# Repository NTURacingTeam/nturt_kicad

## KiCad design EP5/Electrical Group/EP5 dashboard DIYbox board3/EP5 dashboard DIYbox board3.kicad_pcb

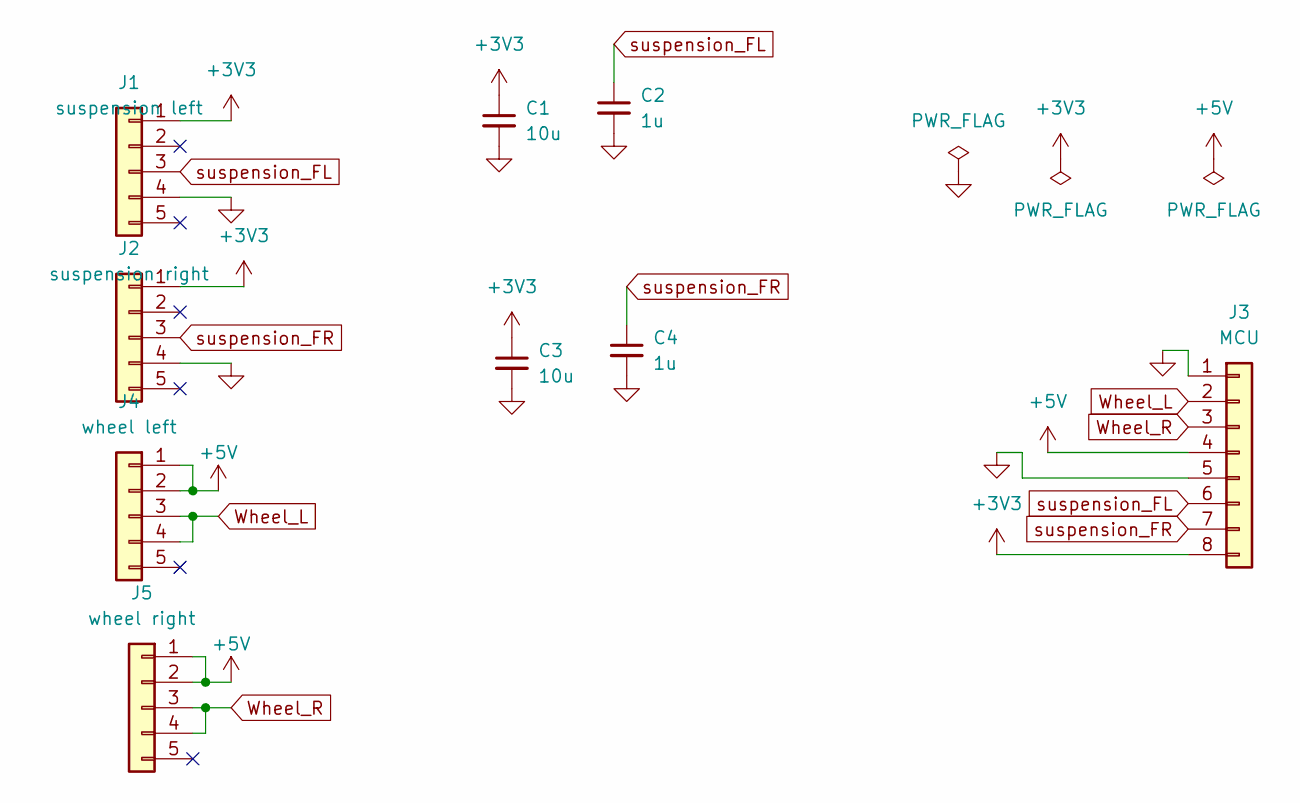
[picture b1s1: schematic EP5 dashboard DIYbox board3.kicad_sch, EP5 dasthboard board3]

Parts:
C1, C3: 10u; C_0805_2012Metric
C2, C4: 1u; C_0805_2012Metric
J1: suspension left; WP-03F3-09-11
J2: suspension right; WP-03F3-09-11
J3: MCU; JST_XH_S8B-XH-A_1x08_P2.50mm_Horizontal
J4: wheel left; WP-04F3-26-11
J5: wheel right; WP-04F3-26-11

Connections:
+3V3: C1.1, C3.1, J1.1, J2.1, J3.8
+5V: J3.4, J4.1, J4.2, J5.1, J5.2
GND: C1.2, C2.2, C3.2, C4.2, J1.4, J2.4, J3.1, J3.5
Wheel_L: J3.2, J4.3, J4.4
Wheel_R: J3.3, J5.3, J5.4
suspension_FL: C2.1, J1.3, J3.6
suspension_FR: C4.1, J2.3, J3.7

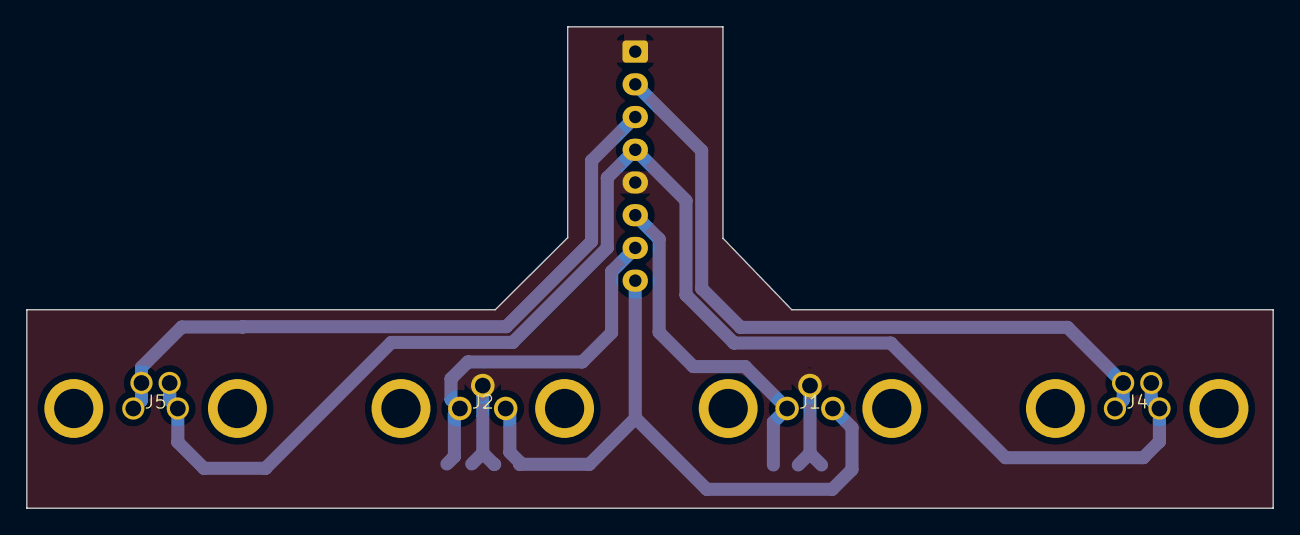
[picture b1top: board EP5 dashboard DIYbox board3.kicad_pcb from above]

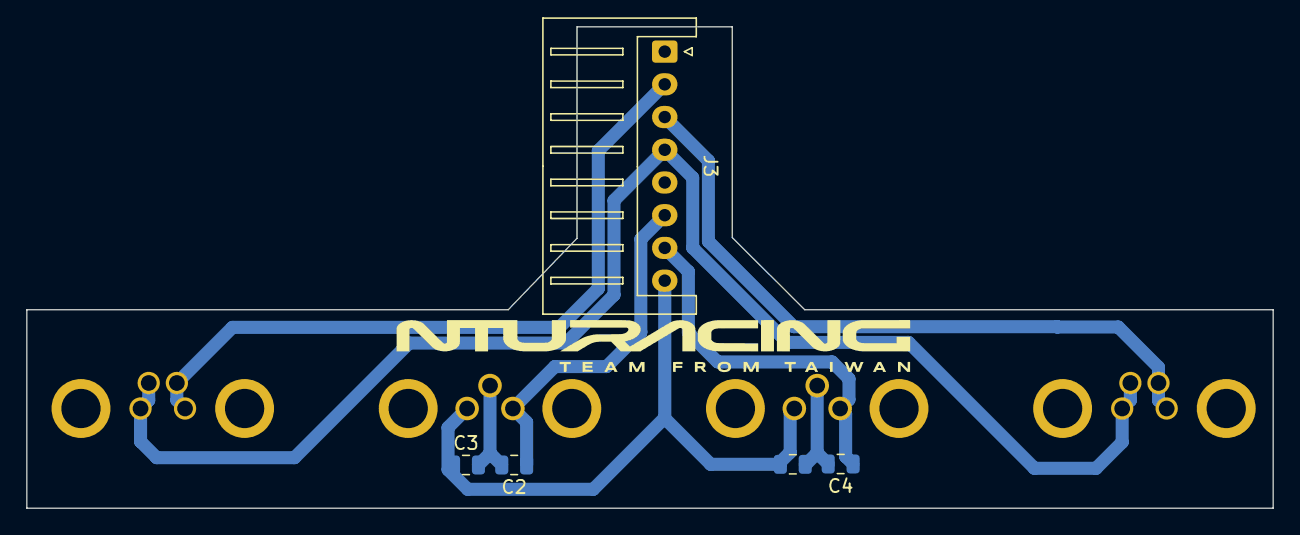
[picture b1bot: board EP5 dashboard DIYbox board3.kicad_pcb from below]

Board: 2 copper layers, 95.2 x 36.8 mm, 9 parts (5 on the bottom side), 7 nets.

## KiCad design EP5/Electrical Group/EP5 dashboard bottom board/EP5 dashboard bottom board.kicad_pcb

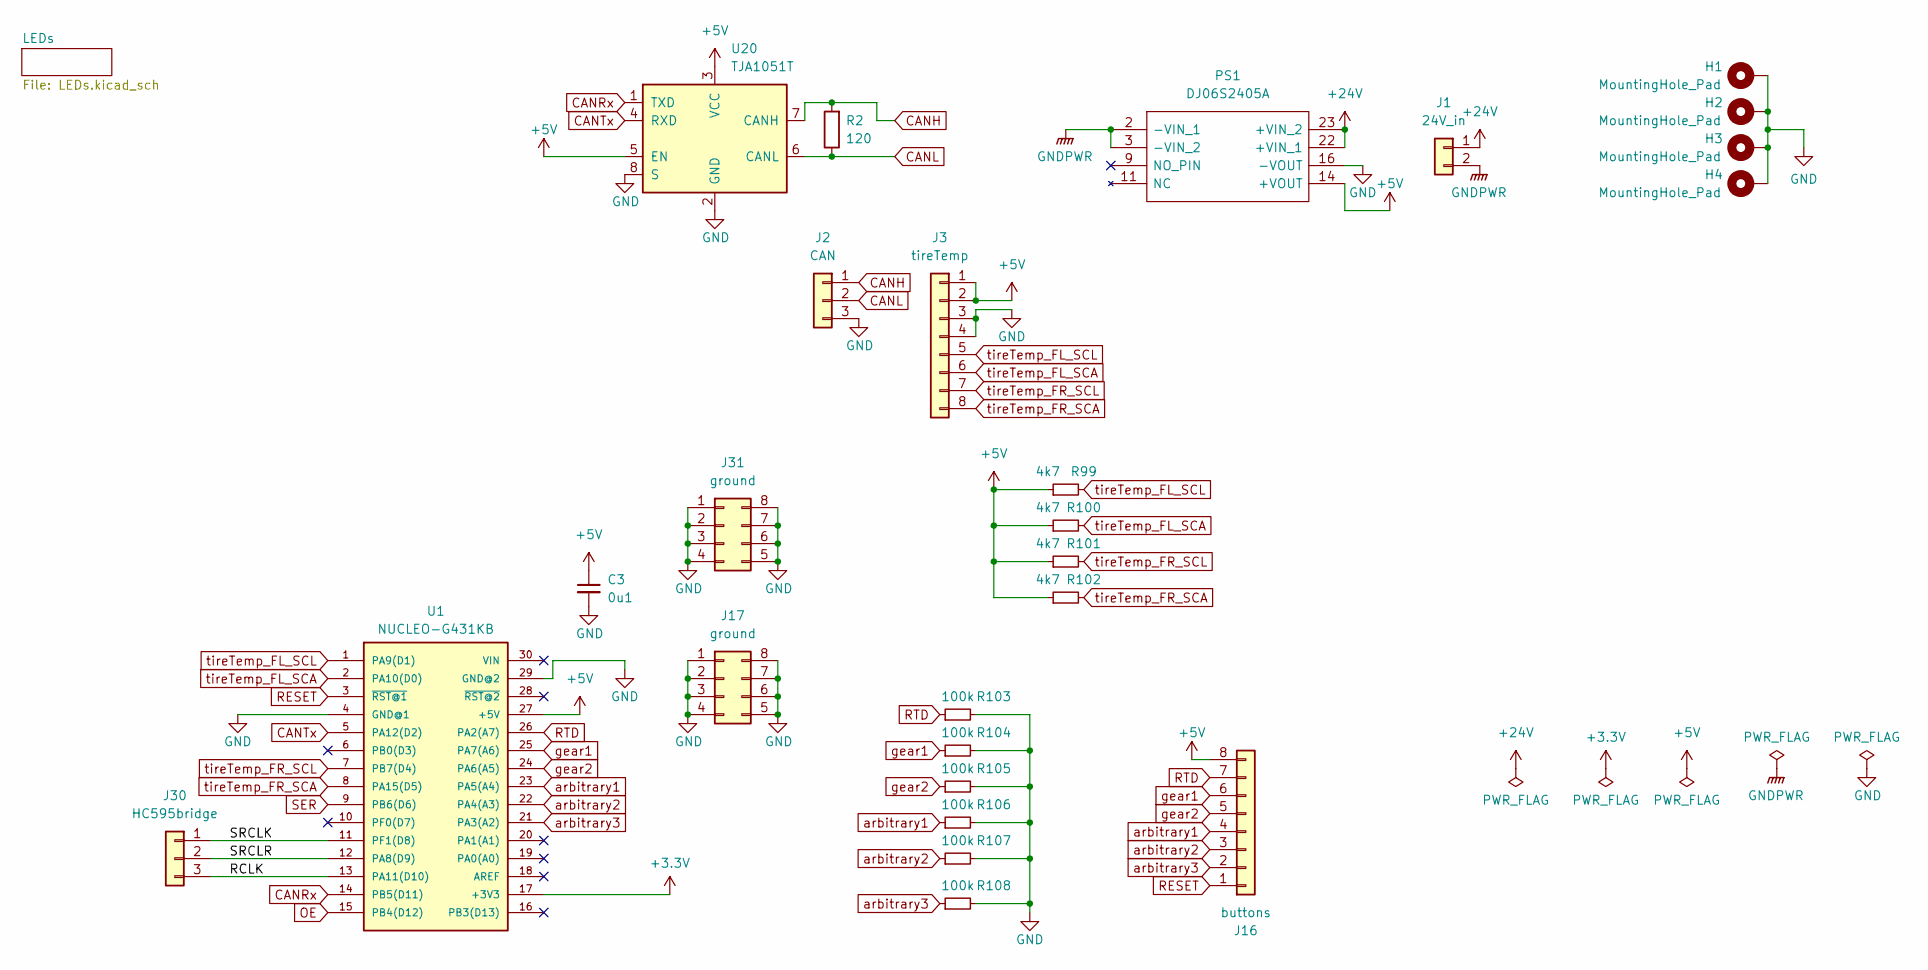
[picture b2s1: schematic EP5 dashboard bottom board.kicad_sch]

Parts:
C3: 0u1; C_0805_2012Metric_Pad1.18x1.45mm_HandSolder
H1, H2, H3, H4: MountingHole_Pad; MountingHole_2.2mm_M2_DIN965_Pad_TopBottom
J1: 24V_in; JST_XH_S2B-XH-A-1_1x02_P2.50mm_Horizontal
J2: CAN; JST_XH_S3B-XH-A-1_1x03_P2.50mm_Horizontal
J3: tireTemp; JST_XH_S8B-XH-A-1_1x08_P2.50mm_Horizontal
J16: buttons; JST_XH_S8B-XH-A-1_1x08_P2.50mm_Horizontal
J17, J31: ground; PinSocket_2x04_P1.27mm_Vertical
J30: HC595bridge; PinSocket_1x03_P1.27mm_Vertical
PS1: DJ06S2405A; DJ06S4805A; Mouser Part Number 108-DJ06S4805A
R2: 120; R_0805_2012Metric
R99, R100, R101, R102: 4k7; R_0805_2012Metric
R103, R104, R105, R106, R107, R108: 100k; R_0805_2012Metric
U1: NUCLEO-G431KB; MANUFACTURER_PART_NUMBER NUCLEO-F303K8
U20: TJA1051T; SOIC-8_3.9x4.9mm_P1.27mm

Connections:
+3.3V: U1.17 (+3V3)
+5V: C3.1, J3.1, J3.2, J16.8, PS1.14 (+VOUT), R99.1, R100.1, R101.1, R102.1, U1.27 (+5V), U20.3 (VCC), U20.5 (EN); also elsewhere on the board
+24V: J1.1, PS1.22 (+VIN_1), PS1.23 (+VIN_2)
/RCLK: J30.3, U1.13 (PA11(D10))
/SRCLK: J30.1, U1.11 (PF1(D8))
/SRCLR: J30.2, U1.12 (PA8(D9))
CANH: J2.1, R2.2, U20.7 (CANH)
CANL: J2.2, R2.1, U20.6 (CANL)
CANRx: U1.14 (PB5(D11)), U20.1 (TXD)
CANTx: U1.5 (PA12(D2)), U20.4 (RXD)
GND: C3.2, H1.1, H2.1, H3.1, H4.1, J2.3, J3.3, J3.4, J17.1, J17.2, J17.3, J17.4, J17.5, J17.6, J17.7, J17.8, J31.1, J31.2, J31.3, J31.4, J31.5, J31.6, J31.7, J31.8, PS1.16 (-VOUT), R103.2, R104.2, R105.2, R106.2, R107.2, R108.2, U1.4 (GND@1), U1.29 (GND@2), U20.2 (GND), U20.8 (S); also elsewhere on the board
GNDPWR: J1.2, PS1.2 (-VIN_1), PS1.3 (-VIN_2)
OE: U1.15 (PB4(D12)); also elsewhere on the board
RESET: J16.1, U1.3 (~RST@1)
RTD: J16.7, R103.1, U1.26 (PA2(A7))
SER: U1.9 (PB6(D6)); also elsewhere on the board
arbitrary1: J16.4, R106.1, U1.23 (PA5(A4))
arbitrary2: J16.3, R107.1, U1.22 (PA4(A3))
arbitrary3: J16.2, R108.1, U1.21 (PA3(A2))
gear1: J16.6, R104.1, U1.25 (PA7(A6))
gear2: J16.5, R105.1, U1.24 (PA6(A5))
tireTemp_FL_SCA: J3.6, R100.2, U1.2 (PA10(D0))
tireTemp_FL_SCL: J3.5, R99.2, U1.1 (PA9(D1))
tireTemp_FR_SCA: J3.8, R102.2, U1.8 (PA15(D5))
tireTemp_FR_SCL: J3.7, R101.2, U1.7 (PB7(D4))

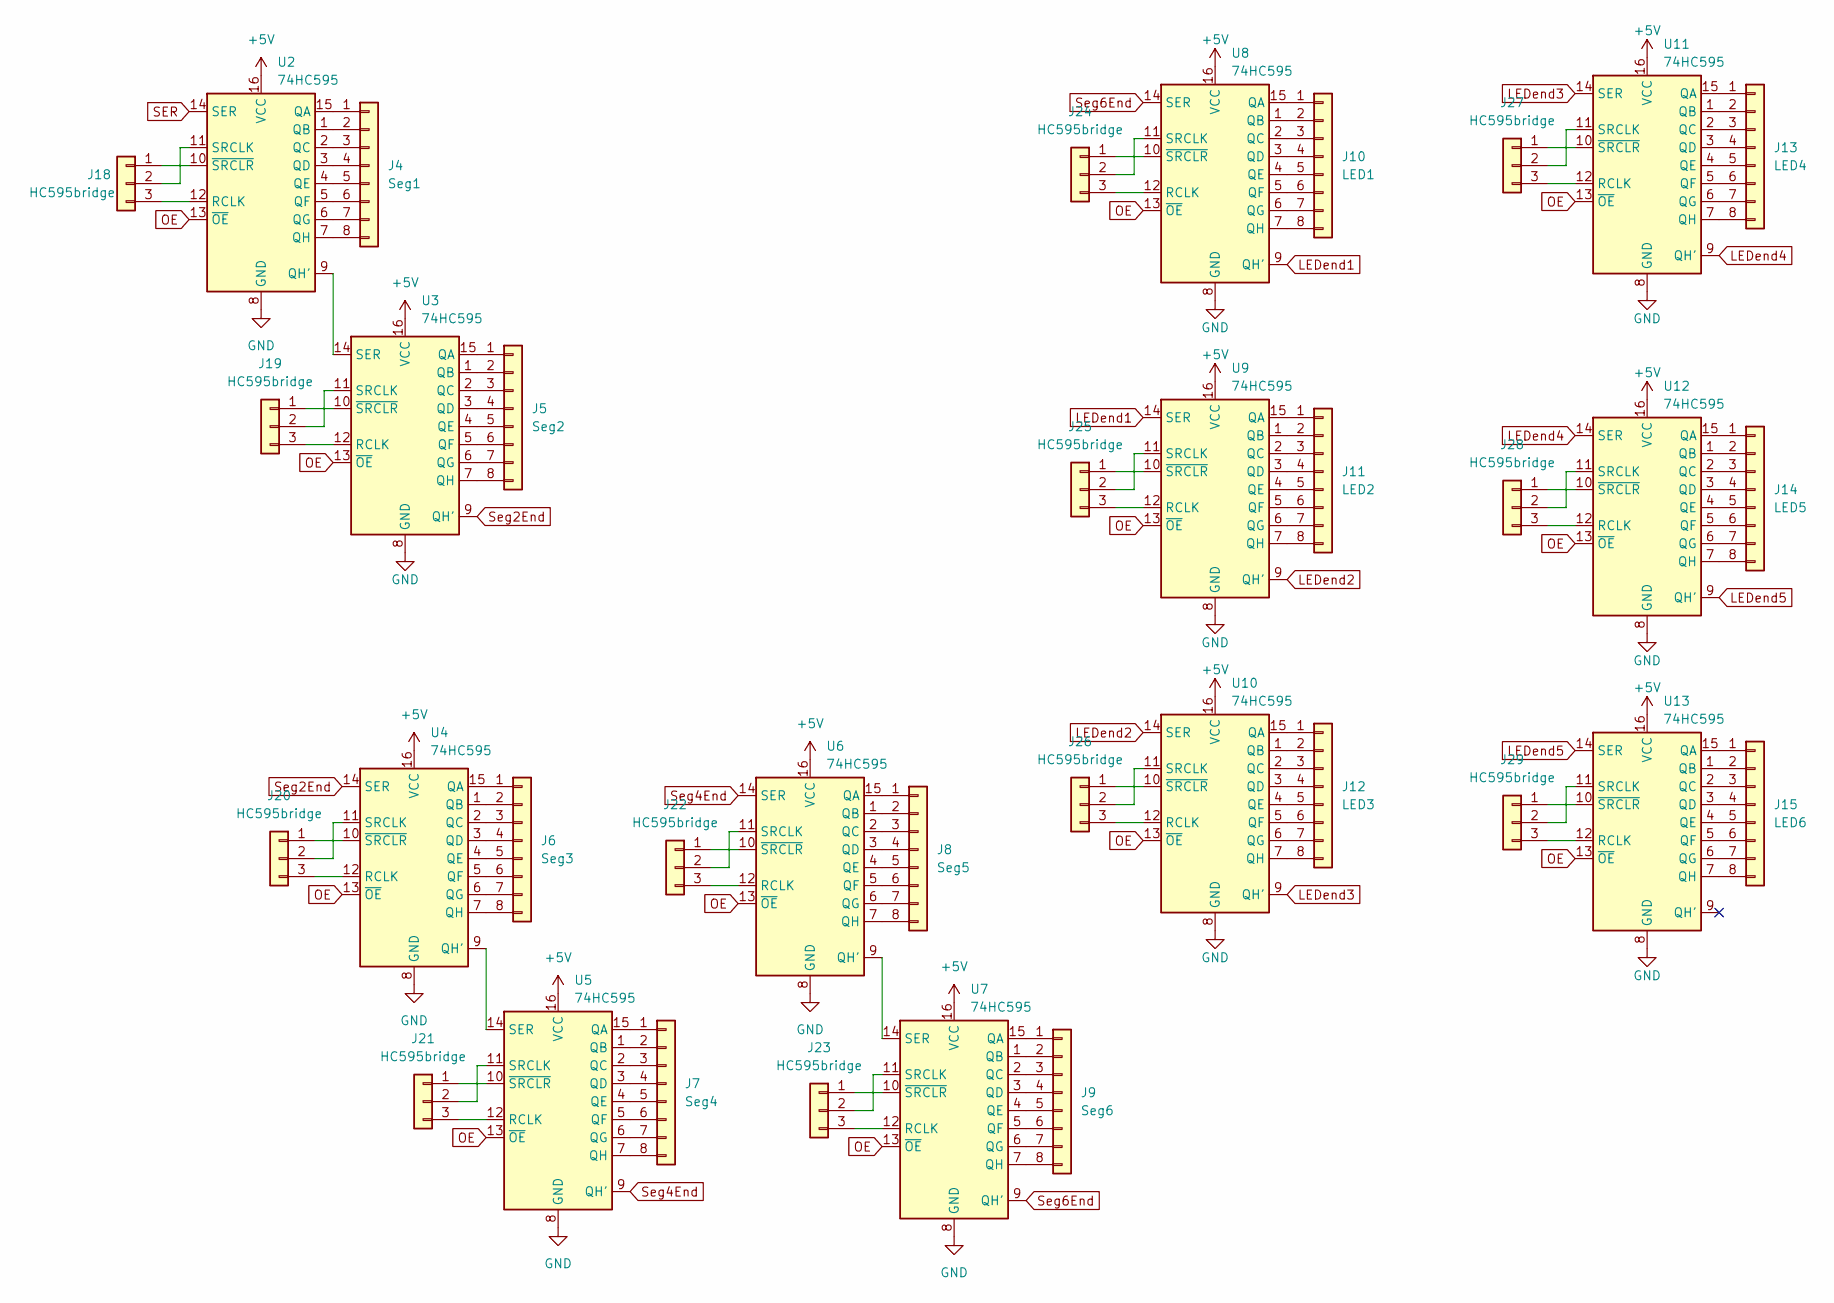
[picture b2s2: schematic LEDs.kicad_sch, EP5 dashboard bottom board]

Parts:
J4: Seg1; PinSocket_1x08_P1.27mm_Vertical
J5: Seg2; PinSocket_1x08_P1.27mm_Vertical
J6: Seg3; PinSocket_1x08_P1.27mm_Vertical
J7: Seg4; PinSocket_1x08_P1.27mm_Vertical
J8: Seg5; PinSocket_1x08_P1.27mm_Vertical
J9: Seg6; PinSocket_1x08_P1.27mm_Vertical
J10: LED1; PinSocket_1x08_P1.27mm_Vertical
J11: LED2; PinSocket_1x08_P1.27mm_Vertical
J12: LED3; PinSocket_1x08_P1.27mm_Vertical
J13: LED4; PinSocket_1x08_P1.27mm_Vertical
J14: LED5; PinSocket_1x08_P1.27mm_Vertical
J15: LED6; PinSocket_1x08_P1.27mm_Vertical
J18, J19, J20, J21, J22, J23, J24, J25, J26, J27, J28, J29: HC595bridge; PinSocket_1x03_P1.27mm_Vertical
U2, U3, U4, U5, U6, U7, U8, U9, U10, U11, U12, U13: 74HC595; SOIC-16_3.9x9.9mm_P1.27mm

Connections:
+5V: U2.16 (VCC), U3.16 (VCC), U4.16 (VCC), U5.16 (VCC), U6.16 (VCC), U7.16 (VCC), U8.16 (VCC), U9.16 (VCC), U10.16 (VCC), U11.16 (VCC), U12.16 (VCC), U13.16 (VCC); also elsewhere on the board
GND: U2.8 (GND), U3.8 (GND), U4.8 (GND), U5.8 (GND), U6.8 (GND), U7.8 (GND), U8.8 (GND), U9.8 (GND), U10.8 (GND), U11.8 (GND), U12.8 (GND), U13.8 (GND); also elsewhere on the board
LEDend1: U8.9 (QH'), U9.14 (SER)
LEDend2: U9.9 (QH'), U10.14 (SER)
LEDend3: U10.9 (QH'), U11.14 (SER)
LEDend4: U11.9 (QH'), U12.14 (SER)
LEDend5: U12.9 (QH'), U13.14 (SER)
unnamed: J4.1, U2.15 (QA)
unnamed: J4.2, U2.1 (QB)
unnamed: J4.3, U2.2 (QC)
unnamed: J4.4, U2.3 (QD)
unnamed: J4.5, U2.4 (QE)
unnamed: J4.6, U2.5 (QF)
unnamed: J4.7, U2.6 (QG)
unnamed: J4.8, U2.7 (QH)
unnamed: J5.1, U3.15 (QA)
unnamed: J5.2, U3.1 (QB)
unnamed: J5.3, U3.2 (QC)
unnamed: J5.4, U3.3 (QD)
unnamed: J5.5, U3.4 (QE)
unnamed: J5.6, U3.5 (QF)
unnamed: J5.7, U3.6 (QG)
unnamed: J5.8, U3.7 (QH)
unnamed: J6.1, U4.15 (QA)
unnamed: J6.2, U4.1 (QB)
unnamed: J6.3, U4.2 (QC)
unnamed: J6.4, U4.3 (QD)
unnamed: J6.5, U4.4 (QE)
unnamed: J6.6, U4.5 (QF)
unnamed: J6.7, U4.6 (QG)
unnamed: J6.8, U4.7 (QH)
unnamed: J7.1, U5.15 (QA)
unnamed: J7.2, U5.1 (QB)
unnamed: J7.3, U5.2 (QC)
unnamed: J7.4, U5.3 (QD)
unnamed: J7.5, U5.4 (QE)
unnamed: J7.6, U5.5 (QF)
unnamed: J7.7, U5.6 (QG)
unnamed: J7.8, U5.7 (QH)
unnamed: J8.1, U6.15 (QA)
unnamed: J8.2, U6.1 (QB)
unnamed: J8.3, U6.2 (QC)
unnamed: J8.4, U6.3 (QD)
unnamed: J8.5, U6.4 (QE)
unnamed: J8.6, U6.5 (QF)
unnamed: J8.7, U6.6 (QG)
unnamed: J8.8, U6.7 (QH)
unnamed: J9.1, U7.15 (QA)
unnamed: J9.2, U7.1 (QB)
unnamed: J9.3, U7.2 (QC)
unnamed: J9.4, U7.3 (QD)
unnamed: J9.5, U7.4 (QE)
unnamed: J9.6, U7.5 (QF)
unnamed: J9.7, U7.6 (QG)
unnamed: J9.8, U7.7 (QH)
unnamed: J10.1, U8.15 (QA)
unnamed: J10.2, U8.1 (QB)
unnamed: J10.3, U8.2 (QC)
unnamed: J10.4, U8.3 (QD)
unnamed: J10.5, U8.4 (QE)
unnamed: J10.6, U8.5 (QF)
unnamed: J10.7, U8.6 (QG)
unnamed: J10.8, U8.7 (QH)
unnamed: J11.1, U9.15 (QA)
unnamed: J11.2, U9.1 (QB)
unnamed: J11.3, U9.2 (QC)
unnamed: J11.4, U9.3 (QD)
unnamed: J11.5, U9.4 (QE)
unnamed: J11.6, U9.5 (QF)
unnamed: J11.7, U9.6 (QG)
unnamed: J11.8, U9.7 (QH)
unnamed: J12.1, U10.15 (QA)
unnamed: J12.2, U10.1 (QB)
unnamed: J12.3, U10.2 (QC)
unnamed: J12.4, U10.3 (QD)
unnamed: J12.5, U10.4 (QE)
unnamed: J12.6, U10.5 (QF)
unnamed: J12.7, U10.6 (QG)
unnamed: J12.8, U10.7 (QH)
unnamed: J13.1, U11.15 (QA)
unnamed: J13.2, U11.1 (QB)
unnamed: J13.3, U11.2 (QC)
unnamed: J13.4, U11.3 (QD)
unnamed: J13.5, U11.4 (QE)
unnamed: J13.6, U11.5 (QF)
unnamed: J13.7, U11.6 (QG)
unnamed: J13.8, U11.7 (QH)
unnamed: J14.1, U12.15 (QA)
unnamed: J14.2, U12.1 (QB)
unnamed: J14.3, U12.2 (QC)
unnamed: J14.4, U12.3 (QD)
unnamed: J14.5, U12.4 (QE)
unnamed: J14.6, U12.5 (QF)
unnamed: J14.7, U12.6 (QG)
unnamed: J14.8, U12.7 (QH)
unnamed: J15.1, U13.15 (QA)
unnamed: J15.2, U13.1 (QB)
unnamed: J15.3, U13.2 (QC)
unnamed: J15.4, U13.3 (QD)
unnamed: J15.5, U13.4 (QE)
unnamed: J15.6, U13.5 (QF)
unnamed: J15.7, U13.6 (QG)
unnamed: J15.8, U13.7 (QH)
unnamed: J18.1, U2.10 (~SRCLR)
unnamed: J18.2, U2.11 (SRCLK)
unnamed: J18.3, U2.12 (RCLK)
unnamed: J19.1, U3.10 (~SRCLR)
unnamed: J19.2, U3.11 (SRCLK)
unnamed: J19.3, U3.12 (RCLK)
unnamed: J20.1, U4.10 (~SRCLR)
unnamed: J20.2, U4.11 (SRCLK)
unnamed: J20.3, U4.12 (RCLK)
unnamed: J21.1, U5.10 (~SRCLR)
unnamed: J21.2, U5.11 (SRCLK)
unnamed: J21.3, U5.12 (RCLK)
unnamed: J22.1, U6.10 (~SRCLR)
unnamed: J22.2, U6.11 (SRCLK)
unnamed: J22.3, U6.12 (RCLK)
unnamed: J23.1, U7.10 (~SRCLR)
unnamed: J23.2, U7.11 (SRCLK)
unnamed: J23.3, U7.12 (RCLK)
unnamed: J24.1, U8.10 (~SRCLR)
unnamed: J24.2, U8.11 (SRCLK)
unnamed: J24.3, U8.12 (RCLK)
unnamed: J25.1, U9.10 (~SRCLR)
unnamed: J25.2, U9.11 (SRCLK)
unnamed: J25.3, U9.12 (RCLK)
unnamed: J26.1, U10.10 (~SRCLR)
unnamed: J26.2, U10.11 (SRCLK)
unnamed: J26.3, U10.12 (RCLK)
unnamed: J27.1, U11.10 (~SRCLR)
unnamed: J27.2, U11.11 (SRCLK)
unnamed: J27.3, U11.12 (RCLK)
unnamed: J28.1, U12.10 (~SRCLR)
unnamed: J28.2, U12.11 (SRCLK)
unnamed: J28.3, U12.12 (RCLK)
unnamed: J29.1, U13.10 (~SRCLR)
unnamed: J29.2, U13.11 (SRCLK)
unnamed: J29.3, U13.12 (RCLK)
unnamed: U2.9 (QH'), U3.14 (SER)
unnamed: U4.9 (QH'), U5.14 (SER)
unnamed: U6.9 (QH'), U7.14 (SER)
OE: U2.13 (~OE), U3.13 (~OE), U4.13 (~OE), U5.13 (~OE), U6.13 (~OE), U7.13 (~OE), U8.13 (~OE), U9.13 (~OE), U10.13 (~OE), U11.13 (~OE), U12.13 (~OE), U13.13 (~OE); also elsewhere on the board
SER: U2.14 (SER); also elsewhere on the board
Seg2End: U3.9 (QH'), U4.14 (SER)
Seg4End: U5.9 (QH'), U6.14 (SER)
Seg6End: U7.9 (QH'), U8.14 (SER)

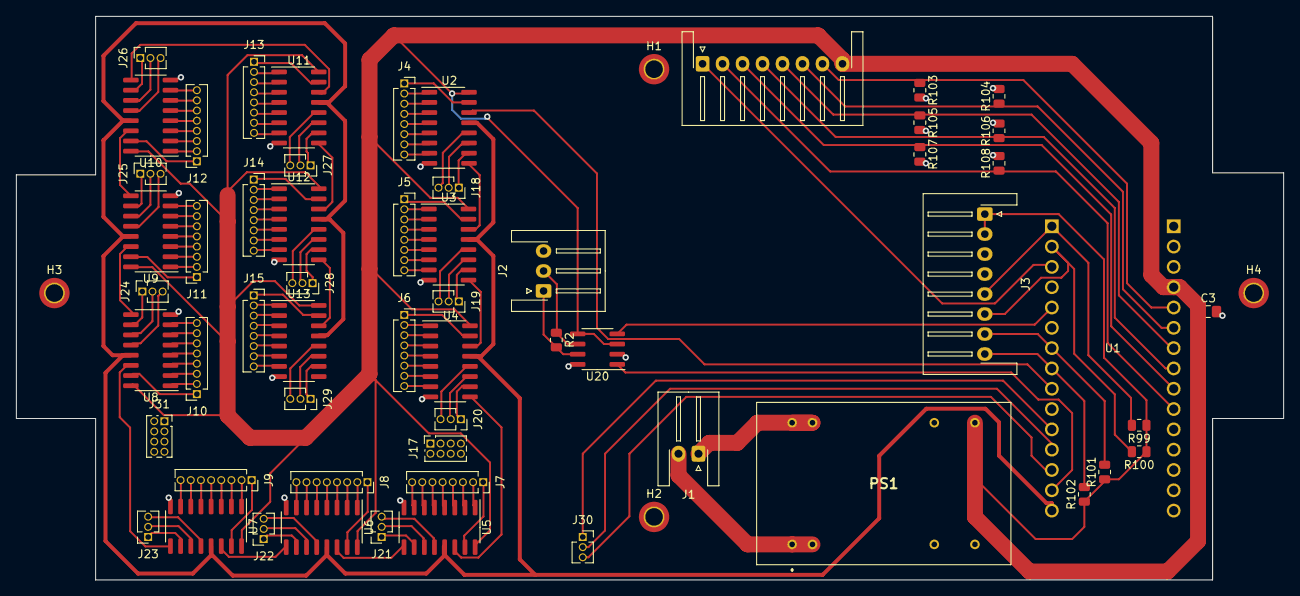
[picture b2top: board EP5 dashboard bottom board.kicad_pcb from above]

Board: 2 copper layers, 158.5 x 70.5 mm, 62 parts (0 on the bottom side), 167 nets.

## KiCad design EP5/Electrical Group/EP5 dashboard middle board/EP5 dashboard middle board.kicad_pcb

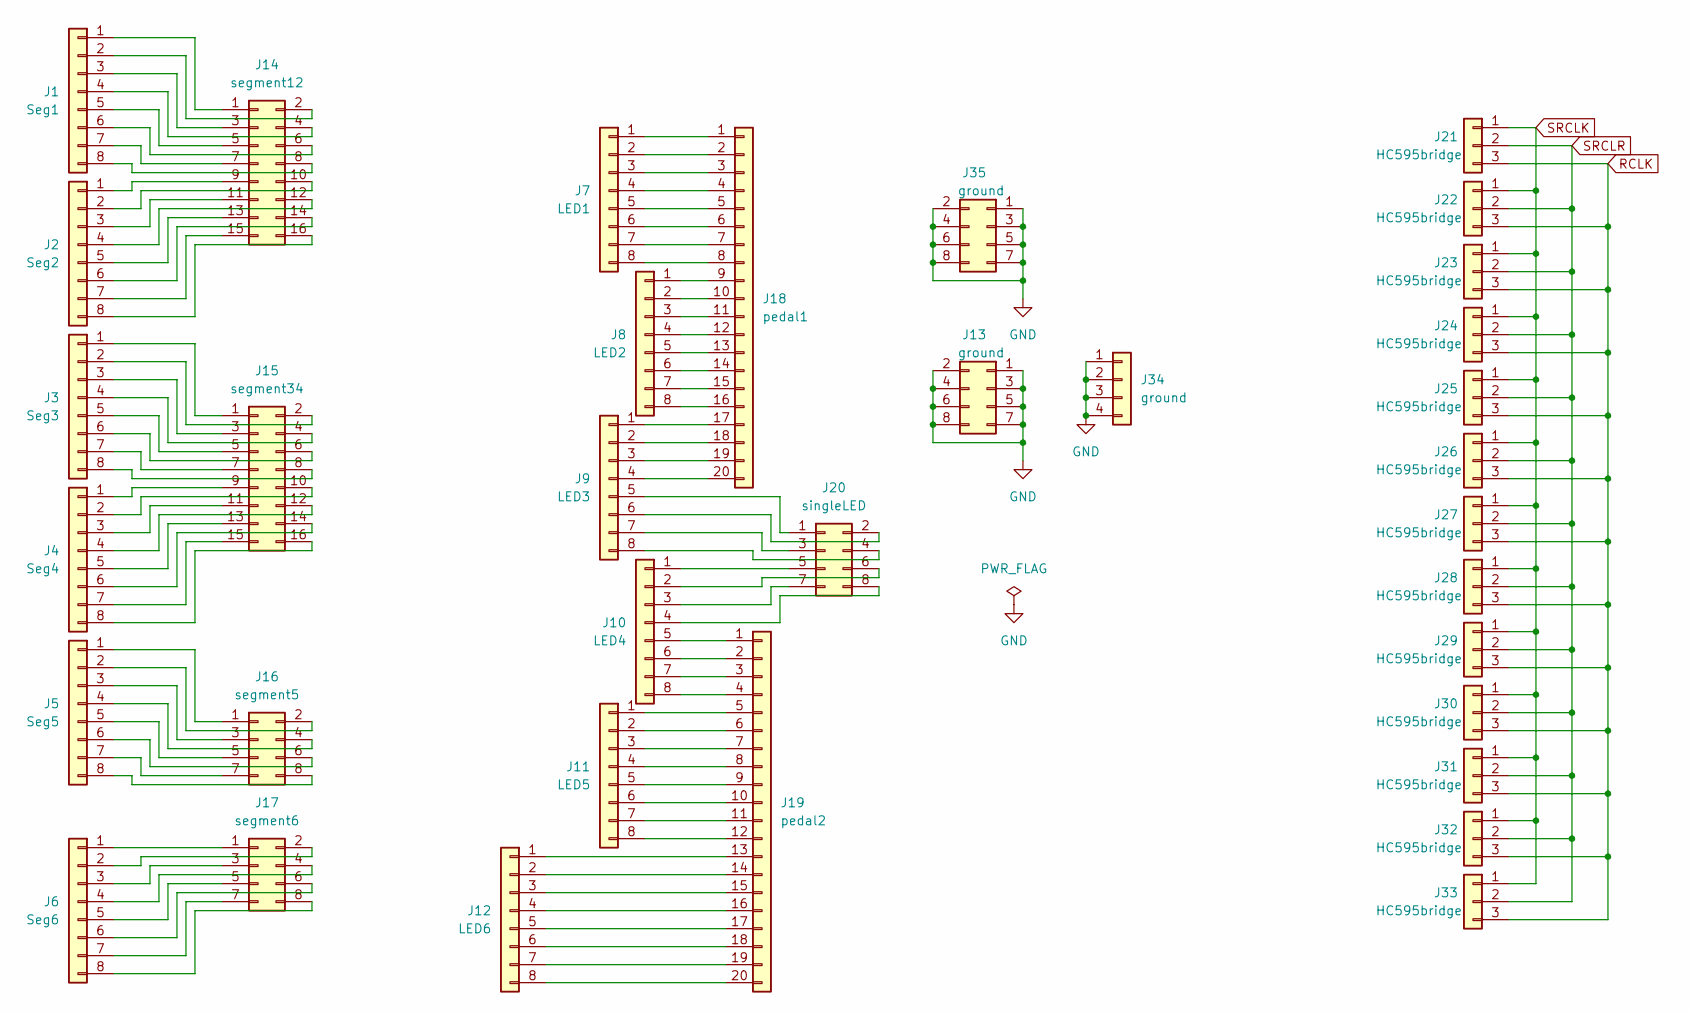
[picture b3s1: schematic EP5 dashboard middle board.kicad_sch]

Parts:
J1: Seg1; PinHeader_1x08_P1.27mm_Vertical
J2: Seg2; PinHeader_1x08_P1.27mm_Vertical
J3: Seg3; PinHeader_1x08_P1.27mm_Vertical
J4: Seg4; PinHeader_1x08_P1.27mm_Vertical
J5: Seg5; PinHeader_1x08_P1.27mm_Vertical
J6: Seg6; PinHeader_1x08_P1.27mm_Vertical
J7: LED1; PinHeader_1x08_P1.27mm_Vertical
J8: LED2; PinHeader_1x08_P1.27mm_Vertical
J9: LED3; PinHeader_1x08_P1.27mm_Vertical
J10: LED4; PinHeader_1x08_P1.27mm_Vertical
J11: LED5; PinHeader_1x08_P1.27mm_Vertical
J12: LED6; PinHeader_1x08_P1.27mm_Vertical
J13, J35: ground; PinHeader_2x04_P1.27mm_Vertical
J14: segment12; PinSocket_2x08_P2.54mm_Vertical
J15: segment34; PinSocket_2x08_P2.54mm_Vertical
J16: segment5; PinSocket_2x04_P2.54mm_Vertical
J17: segment6; PinSocket_2x04_P2.54mm_Vertical
J18: pedal1; PinSocket_1x20_P2.54mm_Vertical
J19: pedal2; PinSocket_1x20_P2.54mm_Vertical
J20: singleLED; PinSocket_2x04_P2.54mm_Vertical
J21, J22, J23, J24, J25, J26, J27, J28, J29, J30, J31, J32, J33: HC595bridge; PinHeader_1x03_P1.27mm_Vertical
J34: ground; PinSocket_1x04_P2.54mm_Vertical

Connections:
GND: J13.1, J13.2, J13.3, J13.4, J13.5, J13.6, J13.7, J13.8, J34.1, J34.2, J34.3, J34.4, J35.1, J35.2, J35.3, J35.4, J35.5, J35.6, J35.7, J35.8
unnamed: J1.1, J14.1
unnamed: J1.2, J14.2
unnamed: J1.3, J14.3
unnamed: J1.4, J14.4
unnamed: J1.5, J14.5
unnamed: J1.6, J14.6
unnamed: J1.7, J14.7
unnamed: J1.8, J14.8
unnamed: J10.1, J20.5
unnamed: J10.2, J20.6
unnamed: J10.3, J20.7
unnamed: J10.4, J20.8
unnamed: J10.5, J19.1
unnamed: J10.6, J19.2
unnamed: J10.7, J19.3
unnamed: J10.8, J19.4
unnamed: J11.1, J19.5
unnamed: J11.2, J19.6
unnamed: J11.3, J19.7
unnamed: J11.4, J19.8
unnamed: J11.5, J19.9
unnamed: J11.6, J19.10
unnamed: J11.7, J19.11
unnamed: J11.8, J19.12
unnamed: J12.1, J19.13
unnamed: J12.2, J19.14
unnamed: J12.3, J19.15
unnamed: J12.4, J19.16
unnamed: J12.5, J19.17
unnamed: J12.6, J19.18
unnamed: J12.7, J19.19
unnamed: J12.8, J19.20
unnamed: J2.1, J14.9
unnamed: J2.2, J14.10
unnamed: J2.3, J14.11
unnamed: J2.4, J14.12
unnamed: J2.5, J14.13
unnamed: J2.6, J14.14
unnamed: J2.7, J14.15
unnamed: J2.8, J14.16
unnamed: J3.1, J15.1
unnamed: J3.2, J15.2
unnamed: J3.3, J15.3
unnamed: J3.4, J15.4
unnamed: J3.5, J15.5
unnamed: J3.6, J15.6
unnamed: J3.7, J15.7
unnamed: J3.8, J15.8
unnamed: J4.1, J15.9
unnamed: J4.2, J15.10
unnamed: J4.3, J15.11
unnamed: J4.4, J15.12
unnamed: J4.5, J15.13
unnamed: J4.6, J15.14
unnamed: J4.7, J15.15
unnamed: J4.8, J15.16
unnamed: J5.1, J16.1
unnamed: J5.2, J16.2
unnamed: J5.3, J16.3
unnamed: J5.4, J16.4
unnamed: J5.5, J16.5
unnamed: J5.6, J16.6
unnamed: J5.7, J16.7
unnamed: J5.8, J16.8
unnamed: J6.1, J17.1
unnamed: J6.2, J17.2
unnamed: J6.3, J17.3
unnamed: J6.4, J17.4
unnamed: J6.5, J17.5
unnamed: J6.6, J17.6
unnamed: J6.7, J17.7
unnamed: J6.8, J17.8
unnamed: J7.1, J18.1
unnamed: J7.2, J18.2
unnamed: J7.3, J18.3
unnamed: J7.4, J18.4
unnamed: J7.5, J18.5
unnamed: J7.6, J18.6
unnamed: J7.7, J18.7
unnamed: J7.8, J18.8
unnamed: J8.1, J18.9
unnamed: J8.2, J18.10
unnamed: J8.3, J18.11
unnamed: J8.4, J18.12
unnamed: J8.5, J18.13
unnamed: J8.6, J18.14
unnamed: J8.7, J18.15
unnamed: J8.8, J18.16
unnamed: J9.1, J18.17
unnamed: J9.2, J18.18
unnamed: J9.3, J18.19
unnamed: J9.4, J18.20
unnamed: J9.5, J20.1
unnamed: J9.6, J20.2
unnamed: J9.7, J20.3
unnamed: J9.8, J20.4
RCLK: J21.3, J22.3, J23.3, J24.3, J25.3, J26.3, J27.3, J28.3, J29.3, J30.3, J31.3, J32.3, J33.3
SRCLK: J21.1, J22.1, J23.1, J24.1, J25.1, J26.1, J27.1, J28.1, J29.1, J30.1, J31.1, J32.1, J33.1
SRCLR: J21.2, J22.2, J23.2, J24.2, J25.2, J26.2, J27.2, J28.2, J29.2, J30.2, J31.2, J32.2, J33.2

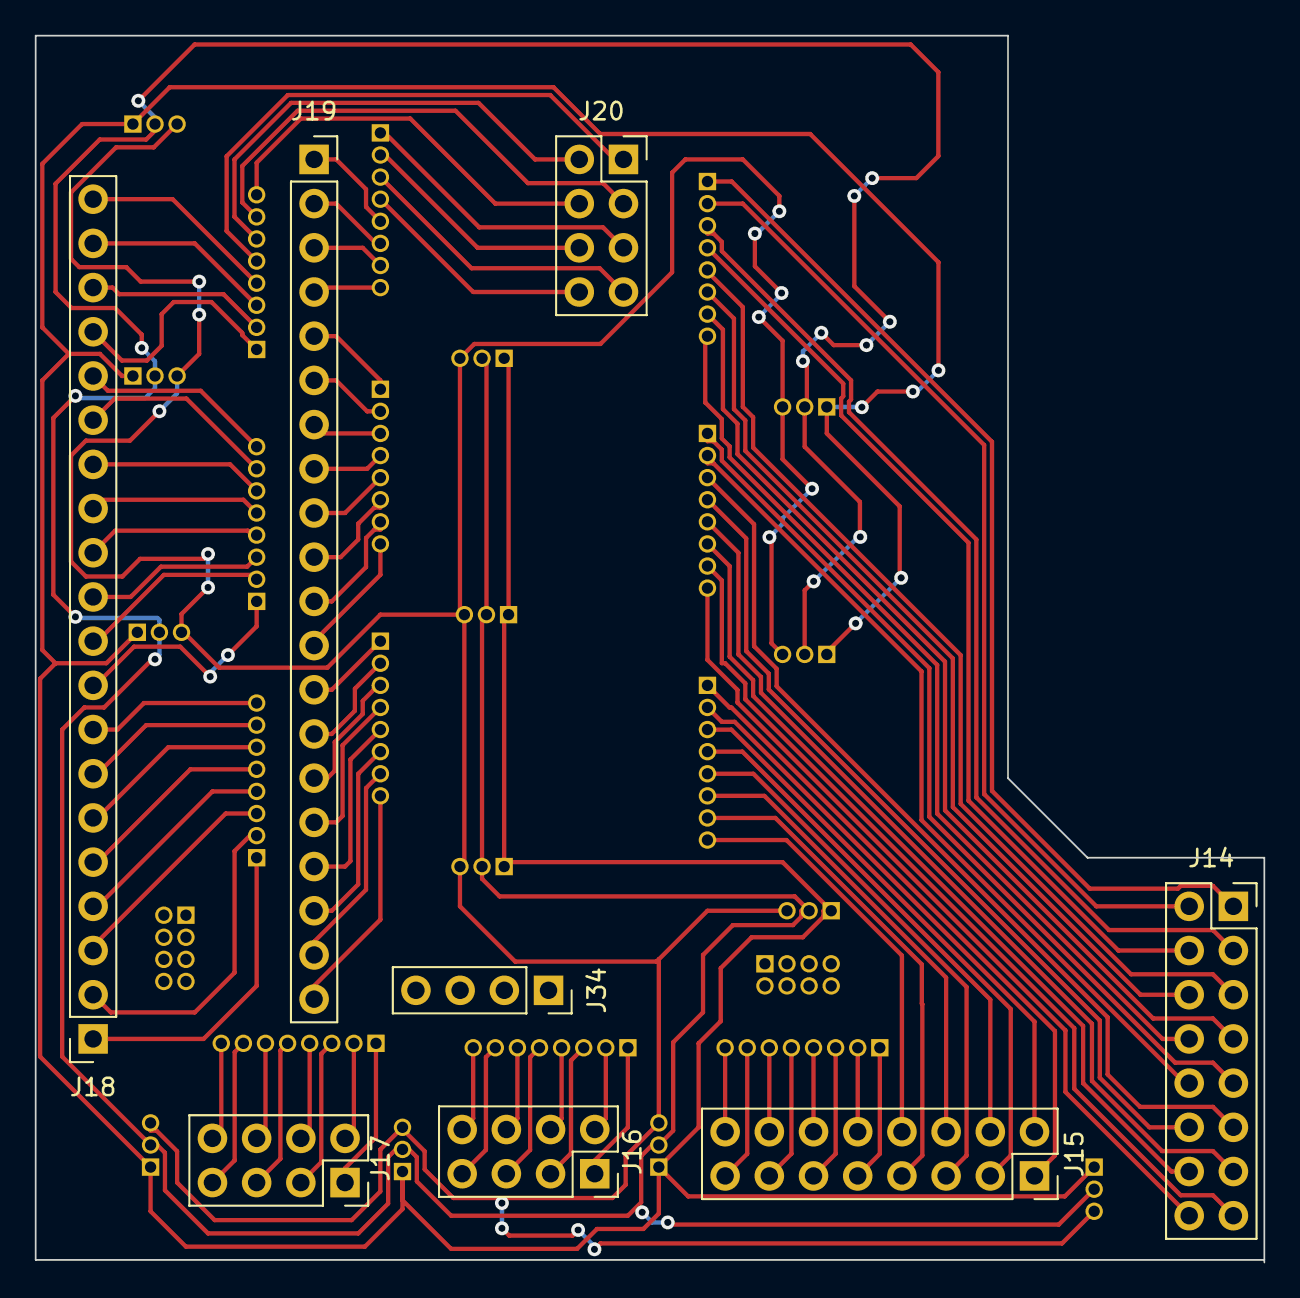
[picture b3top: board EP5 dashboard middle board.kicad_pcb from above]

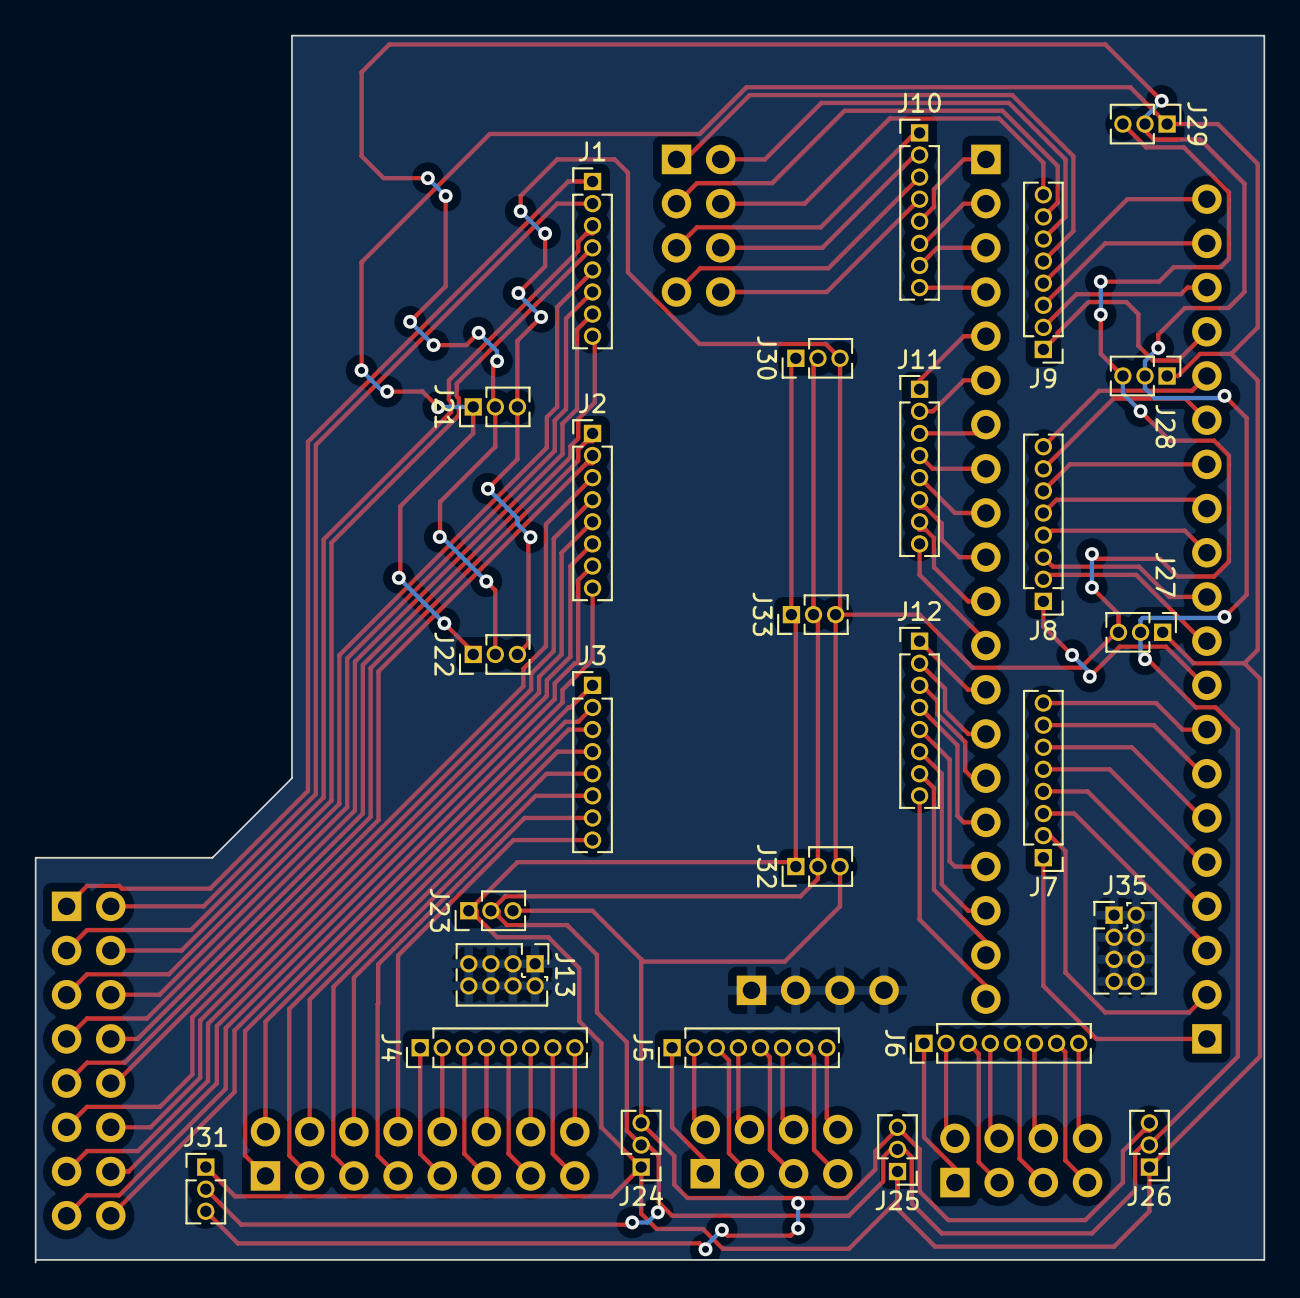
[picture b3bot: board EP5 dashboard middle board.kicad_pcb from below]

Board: 2 copper layers, 70.6 x 70.5 mm, 35 parts (27 on the bottom side), 100 nets.
